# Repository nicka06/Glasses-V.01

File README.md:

# Glasses-V.01

This repo shows a pair of "AI" glasses that use a microphone, speaker, and microcontroller to allow users to have siri at all times (when on wifi). They'll be able to ask questions, complete tasks, and be more efficient with these glasses. While these glasses have only audio, it is a first step towareds glasses with cameras and more. This is my personal end goal for this project. Just a stepping stone towards more advance glasses work. (Hence the V0.1 repo name). If you have any questions, feel free to reach out. 

|Part                        |Part Number                             |# of parts|snapeda link                                                                                                                                                                                                                                                                                                                                                                                                                                                                                                                                                                                                                                                                           |Price|Actual Link                                                                                                                                                                                                                                                                                                                                                                                                                                                                                                                                                                                                                                                                            |Total Price|
|----------------------------|----------------------------------------|----------|---------------------------------------------------------------------------------------------------------------------------------------------------------------------------------------------------------------------------------------------------------------------------------------------------------------------------------------------------------------------------------------------------------------------------------------------------------------------------------------------------------------------------------------------------------------------------------------------------------------------------------------------------------------------------------------|-----|---------------------------------------------------------------------------------------------------------------------------------------------------------------------------------------------------------------------------------------------------------------------------------------------------------------------------------------------------------------------------------------------------------------------------------------------------------------------------------------------------------------------------------------------------------------------------------------------------------------------------------------------------------------------------------------|-----------|
|Microcontroller             |ESP32-S3-WROOM-1-N16R8                  |1         |https://www.snapeda.com/parts/ESP32-S3-WROOM-1-N16R8/Espressif%20Systems/view-part/?ref=search&t=ESP32-S3-WROOM-1-N16R8&ab_test_case=b                                                                                                                                                                                                                                                                                                                                                                                                                                                                                                                                                 |6.56 |https://www.digikey.com/en/products/detail/espressif-systems/ESP32-S3-WROOM-1-N16R8/16163954?gad_source=1&gad_campaignid=20783325532&gbraid=0AAAAADrbLlhoX6jquTGZxW9rgvqGXhdUZ&gclid=CjwKCAjwp_LDBhBCEiwAK7Fnkuxh-Wv312ccLeRvQl4KA0CQU8T0WVN-HfHrd-JbklPjBEjkM-3N1hoC2ZgQAvD_BwE&gclsrc=aw.ds                                                                                                                                                                                                                                                                                                                                                                                          |13.12      |
|Microphone                  |ICS-43434                               |1         |https://www.snapeda.com/parts/ICS-43434/TDK%20InvenSense/view-part/?ref=tdk%20invensense_in&t=ICS-43434&con_ref=None                                                                                                                                                                                                                                                                                                                                                                                                                                                                                                                                                                   |2.98 |https://www.digikey.com/en/products/detail/tdk-invensense/ICS-43434/6140298?utm_campaign=buynow&utm_medium=aggregator&utm_source=snapeda                                                                                                                                                                                                                                                                                                                                                                                                                                                                                                                                               |5.96       |
|Amplifier                   |MAX98357AETE+T                          |1         |http://snapeda.com/parts/MAX98357AETE%2BT/Analog%20Devices/view-part/?ref=search&t=MAX98357AETE%2BT&ab_test_case=b                                                                                                                                                                                                                                                                                                                                                                                                                                                                                                                                                                     |3.19 |https://www.digikey.com/en/products/detail/analog-devices-inc-maxim-integrated/MAX98357AETE-T/4936122?utm_campaign=buynow&utm_medium=aggregator&utm_source=snapeda                                                                                                                                                                                                                                                                                                                                                                                                                                                                                                                     |6.38       |
|Speaker                     |KDMG151508-05                           |1         |https://www.snapeda.com/parts/KDMG151508-05/Kingstate/view-part/?ref=search&t=KDMG151508-05                                                                                                                                                                                                                                                                                                                                                                                                                                                                                                                                                                                            |2.12 |https://www.digikey.com/en/products/detail/db-unlimited/SM150908-2/9990586?gad_source=1&gad_campaignid=20243136172&gbraid=0AAAAADrbLlgid6KqDNBHULPHGtDjBGKy6&gclid=CjwKCAjwp_LDBhBCEiwAK7Fnknqfs3PqYxI0d2qcRMip4_ntUb9yY7HQQ-hDFoptXZGg9NlflI530RoCsUwQAvD_BwE&gclsrc=aw.ds                                                                                                                                                                                                                                                                                                                                                                                                            |4.24       |
|Battery                     |1570 Lithium Polymer Battery 3.7V 100mAh|1         |https://www.snapeda.com/parts/1570/Adafruit%20Industries/view-part/?ref=search&t=Lithium%20Ion%20Polymer%20Battery%20with%20Short%20Cable%20-%203.7V%20200mAh&ab_test_case=b                                                                                                                                                                                                                                                                                                                                                                                                                                                                                                           |5.95 |https://www.digikey.com/en/products/detail/adafruit-industries-llc/1570/5054546?utm_campaign=buynow&utm_medium=aggregator&utm_source=snapeda                                                                                                                                                                                                                                                                                                                                                                                                                                                                                                                                           |11.9       |
|Charge Management Controller|MCP73831T-2ACI/OT                       |1         |https://www.snapeda.com/parts/MCP73831T-2ACI/OT/Microchip%20Technology/view-part/?ref=search&t=MCP73831&ab_test_case=b                                                                                                                                                                                                                                                                                                                                                                                                                                                                                                                                                                 |0.76 |https://www.digikey.com/en/products/detail/microchip-technology/MCP73831T-2ACI-OT/964301?utm_campaign=buynow&utm_medium=aggregator&utm_source=snapeda                                                                                                                                                                                                                                                                                                                                                                                                                                                                                                                                  |1.52       |
|                            |TLV62568DBVR                            |1         |https://www.snapeda.com/parts/2340901-1/TE%20Connectivity/view-part/?ref=search&t=2340901-1&ab_test_case=b                                                                                                                                                                                                                                                                                                                                                                                                                                                                                                                                                                             |0.23 |https://www.digikey.com/en/products/detail/texas-instruments/TLV62568DBVR/6588886?utm_campaign=buynow&utm_medium=aggregator&utm_source=snapeda                                                                                                                                                                                                                                                                                                                                                                                                                                                                                                                                         |0.46       |
|USB C Port                  |2340901-1                               |1         |https://www.snapeda.com/parts/2340901-1/TE%20Connectivity/view-part/?ref=search&t=2340901-1&ab_test_case=b                                                                                                                                                                                                                                                                                                                                                                                                                                                                                                                                                                             |0.7  |https://www.digikey.com/en/products/detail/gct/USB4500-03-0-A/15283206                                                                                                                                                                                                                                                                                                                                                                                                                                                                                                                                                                                                                 |1.4        |
|Battery Connector (white)   |B2B-PH-K-S (LF)(SN)                     |1         |https://www.snapeda.com/parts/B2B-PH-K-S%20%28LF%29%28SN%29/JST/view-part/?ref=search&t=B2B-PH-K-S&ab_test_case=b                                                                                                                                                                                                                                                                                                                                                                                                                                                                                                                                                                      |0.1  |https://www.digikey.com/en/products/detail/jst-sales-america-inc/B2B-XH-A/1651045?gad_source=1&gad_campaignid=20783325532&gbraid=0AAAAADrbLlhoX6jquTGZxW9rgvqGXhdUZ&gclid=CjwKCAjwp_LDBhBCEiwAK7FnkiGOrYvskTYfoYS7-Bnt9eSlk76hj8uJJX4-BQsrg9oAHQYzmg24FBoCVZsQAvD_BwE&gclsrc=aw.ds                                                                                                                                                                                                                                                                                                                                                                                                     |0.2        |
|Manual Switch               |PCM12SMTR                               |1         |https://www.snapeda.com/parts/PCM12SMTR/Littelfuse%2FC%26K/view-part/?ref=search&t=PCM12SMTR&ab_test_case=b                                                                                                                                                                                                                                                                                                                                                                                                                                                                                                                                                                            |0.8  |https://www.snapeda.com/parts/PCM12SMTR/Littelfuse%2FC%26K/view-part/?ref=search&t=PCM12SMTR&ab_test_case=b                                                                                                                                                                                                                                                                                                                                                                                                                                                                                                                                                                            |1.6        |
|LED Blue Light              |LTST-C191TBKT                           |1         |https://www.snapeda.com/parts/LTST-C191TBKT/Lite-On%20Electronics/view-part/?ref=dk&t=LTST-C191TBKT&con_ref=None&ab_test_case=b                                                                                                                                                                                                                                                                                                                                                                                                                                                                                                                                                        |0.24 |https://www.digikey.com/en/products/detail/liteon/LTST-C191TBKT/388530?utm_source=snapeda&utm_medium=aggregator&utm_campaign=buynow                                                                                                                                                                                                                                                                                                                                                                                                                                                                                                                                                    |0.48       |
|LED Red Light               |LTST-C191KRKT                           |1         |https://www.snapeda.com/parts/LTST-C191KRKT/Lite-On%20Inc./view-part/?ref=dk&t=LTST-C191KRKT&con_ref=None&ab_test_case=b                                                                                                                                                                                                                                                                                                                                                                                                                                                                                                                                                               |0.15 |https://www.digikey.com/en/products/detail/liteon/LTST-C191KRKT/386837?utm_source=snapeda&utm_medium=aggregator&utm_campaign=buynow                                                                                                                                                                                                                                                                                                                                                                                                                                                                                                                                                    |0.3        |
|5.1k Resistor               |ERA-3ARB512V                            |3         |https://www.snapeda.com/parts/ERA-3ARB512V/Panasonic/view-part/?ref=search&t=ERA-3ARB512V&ab_test_case=b                                                                                                                                                                                                                                                                                                                                                                                                                                                                                                                                                                               |0.35 |https://www.digikey.com/en/products/detail/panasonic-electronic-components/ERA-3ARB512V/3073669?utm_campaign=buynow&utm_medium=aggregator&utm_source=snapeda                                                                                                                                                                                                                                                                                                                                                                                                                                                                                                                           |2.1        |
|10k resistor                |CR0603AFX-1002EAS                       |2         |https://www.snapeda.com/parts/CR0603AFX-1002EAS/Bourns/view-part/?ref=search&t=CR0603AFX-1002EAS&ab_test_case=b                                                                                                                                                                                                                                                                                                                                                                                                                                                                                                                                                                        |0.1  |https://www.digikey.com/en/products/detail/bourns-inc/CR0603AFX-1002EAS/10240117?utm_campaign=buynow&utm_medium=aggregator&utm_source=snapeda                                                                                                                                                                                                                                                                                                                                                                                                                                                                                                                                          |0.4        |
|220hms Resistor             |WK73R1JTTD2200F                         |2         |https://www.snapeda.com/parts/WK73R1JTTD2200F/KOA%20Speer/view-part/?ref=search&t=WK73R1JTTD2200F&ab_test_case=b                                                                                                                                                                                                                                                                                                                                                                                                                                                                                                                                                                       |0.12 |https://www.mouser.com/ProductDetail/KOA-Speer/WK73R1JTTD2200F?utm_campaign=mouser&qs=xhbEVWpZdWcwQMv%2FxntCbQ%3D%3D&utm_medium=online&utm_source=snapedaonline&utm_content=model                                                                                                                                                                                                                                                                                                                                                                                                                                                                                                      |0.48       |
|100nf capacitor             |885012206071                            |4         |https://www.snapeda.com/parts/885012206071/W%C3%BCrth%20Elektronik/view-part/?ref=dk&t=%200603%20Ceramic%20100nF&con_ref=None&ab_test_case=b                                                                                                                                                                                                                                                                                                                                                                                                                                                                                                                                           |0.1  |https://www.digikey.com/en/products/detail/w%C3%BCrth-elektronik/885012206071/5453844?utm_source=snapeda&utm_medium=aggregator&utm_campaign=buynow                                                                                                                                                                                                                                                                                                                                                                                                                                                                                                                                     |0.8        |
|4.7u capitor                |CL10A475KA8NQNC                         |1         |https://www.snapeda.com/parts/CL10A475KA8NQNC/Samsung/view-part/?ref=me&t=%200603%20Ceramic%204.7%C2%B5F&con_ref=None&ab_test_case=b                                                                                                                                                                                                                                                                                                                                                                                                                                                                                                                                                   |0.23 |https://www.mouser.com/ProductDetail/Samsung-Electro-Mechanics/CL10A475KA8NQNC?qs=9nYkJLYMUzsiOkP%2FacWBkg%3D%3D&utm_source=snapedaonline&utm_medium=online&utm_campaign=mouser&utm_content=partpage                                                                                                                                                                                                                                                                                                                                                                                                                                                                                   |0.46       |
|10uf capictor               |GRM188R61A106MAALD                      |2         |https://www.snapeda.com/parts/GRM188R61A106MAALD/Murata/view-part/?ref=dk&t=%200603%20Ceramic%2010%C2%B5F&con_ref=None&ab_test_case=b                                                                                                                                                                                                                                                                                                                                                                                                                                                                                                                                                  |0.22 |https://www.digikey.com/en/products/detail/murata-electronics/GRM188R61A106MAALD/4905335?utm_source=snapeda&utm_medium=aggregator&utm_campaign=buynow                                                                                                                                                                                                                                                                                                                                                                                                                                                                                                                                  |0.88       |
|22uf capictor               |C1608X5R0J226M080AC                     |1         |https://www.snapeda.com/parts/C1608X5R0J226M080AC/TDK/view-part/?ref=dk&t=%200603%20Ceramic%2022%C2%B5F&con_ref=None&ab_test_case=b                                                                                                                                                                                                                                                                                                                                                                                                                                                                                                                                                    |0.27 |https://www.digikey.com/en/products/detail/tdk-corporation/C1608X5R0J226M080AC/2792254?utm_source=snapeda&utm_medium=aggregator&utm_campaign=buynow                                                                                                                                                                                                                                                                                                                                                                                                                                                                                                                                    |0.54       |
|2.2 inductor                |DFE252012F-2R2M=P2                      |1         |https://www.snapeda.com/parts/DFE252012F-2R2M%3DP2/Murata/view-part/?ref=search&t=DFE252012F-2R2M%3DP2&ab_test_case=b                                                                                                                                                                                                                                                                                                                                                                                                                                                                                                                                                                  |0.24 |https://www.digikey.com/en/products/detail/murata-electronics/DFE252012F-2R2M-P2/5812591?utm_campaign=buynow&utm_medium=aggregator&utm_source=snapeda                                                                                                                                                                                                                                                                                                                                                                                                                                                                                                                                  |0.48       |
|ESD Protector               |TPD2E001DRLRG4                          |1         |https://www.snapeda.com/parts/TPD2E001DRLRG4/Texas%20Instruments/view-part/?ref=search&t=TPD2E001DRLR&ab_test_case=b                                                                                                                                                                                                                                                                                                                                                                                                                                                                                                                                                                   |0.77 |https://www.digikey.com/en/products/detail/texas-instruments/TPD2E001DRLRG4/1907452?utm_campaign=buynow&utm_medium=aggregator&utm_source=snapeda                                                                                                                                                                                                                                                                                                                                                                                                                                                                                                                                       |1.54       |
|1u capitor                  |885012206026                            |1         |https://www.snapeda.com/parts/885012206026/W%C3%BCrth%20Elektronik/view-part/?ref=search&t=1%C2%B5F%2010V%200603%20ceramic%20capacitor&ab_test_case=b                                                                                                                                                                                                                                                                                                                                                                                                                                                                                                                                  |0.27 |https://www.digikey.com/en/products/detail/w%C3%BCrth-elektronik/885012206026/5453800?utm_campaign=buynow&utm_medium=aggregator&utm_source=snapeda                                                                                                                                                                                                                                                                                                                                                                                                                                                                                                                                     |0.54       |
|Switch Button               |TL3315NF160Q                            |1         |https://www.snapeda.com/parts/TL3315NF160Q/E-Switch/view-part/?ref=search&t=tl3315nf160Q                                                                                                                                                                                                                                                                                                                                                                                                                                                                                                                                                                                               |0.15 |https://www.digikey.com/en/products/detail/e-switch/TL3315NF160Q/1870395?utm_campaign=buynow&utm_medium=aggregator&utm_source=snapeda                                                                                                                                                                                                                                                                                                                                                                                                                                                                                                                                                  |0.3        |
|3d Printing filament        |N/A                                     |1         |https://www.amazon.com/eSUN-Filament-Printing-Printer-Designed/dp/B0DGQBMJMK/ref=sr_1_16?dib=eyJ2IjoiMSJ9.Razt1k5uVOV2TzDUjSQvl7XEcxdtlHmAdZQWosMeTQ50CwFn7o1y91poBYqmVyD9HxIA_A0r02FOmVlrp1nPMesRN62hAAydwv-PxE5Qi07-Ww0ryQYsGgAqZsrmEU20zU0_ffjW8d8uhPSc8SdO0CSTQG0t-tMYp2xMcieXr8z_RaTrzCr2jQG8r_7wSBk8uNSQbhB2PLppIrgodCKK9YNonEEP75L9N3QZLqYCnD0.fJtDJZ7egESpQDcGEz5eu_KVAuM1CXnrID5a33sKsjs&dib_tag=se&hvadid=695206731837&hvdev=c&hvexpln=67&hvlocphy=9190255&hvnetw=g&hvocijid=9219964727381373825--&hvqmt=e&hvrand=9219964727381373825&hvtargid=kwd-320787596539&hydadcr=8497_13654088&keywords=pla%2Bamazon&mcid=987f97c45f7b3a3dac93ebf26610d89d&qid=1754454039&sr=8-16&th=1|11.39|https://www.amazon.com/eSUN-Filament-Printing-Printer-Designed/dp/B0DGQBMJMK/ref=sr_1_16?dib=eyJ2IjoiMSJ9.Razt1k5uVOV2TzDUjSQvl7XEcxdtlHmAdZQWosMeTQ50CwFn7o1y91poBYqmVyD9HxIA_A0r02FOmVlrp1nPMesRN62hAAydwv-PxE5Qi07-Ww0ryQYsGgAqZsrmEU20zU0_ffjW8d8uhPSc8SdO0CSTQG0t-tMYp2xMcieXr8z_RaTrzCr2jQG8r_7wSBk8uNSQbhB2PLppIrgodCKK9YNonEEP75L9N3QZLqYCnD0.fJtDJZ7egESpQDcGEz5eu_KVAuM1CXnrID5a33sKsjs&dib_tag=se&hvadid=695206731837&hvdev=c&hvexpln=67&hvlocphy=9190255&hvnetw=g&hvocijid=9219964727381373825--&hvqmt=e&hvrand=9219964727381373825&hvtargid=kwd-320787596539&hydadcr=8497_13654088&keywords=pla%2Bamazon&mcid=987f97c45f7b3a3dac93ebf26610d89d&qid=1754454039&sr=8-16&th=1|11.39      |
|PCB                         |N/A                                     |1         |N/A                                                                                                                                                                                                                                                                                                                                                                                                                                                                                                                                                                                                                                                                                    |2    |N/A                                                                                                                                                                                                                                                                                                                                                                                                                                                                                                                                                                                                                                                                                    |2          |
|                            |                                        |          |                                                                                                                                                                                                                                                                                                                                                                                                                                                                                                                                                                                                                                                                                       |     |                                                                                                                                                                                                                                                                                                                                                                                                                                                                                                                                                                                                                                                                                       |69.47      |
                                                                                                                                                                                                                                                                                    |56.08      |

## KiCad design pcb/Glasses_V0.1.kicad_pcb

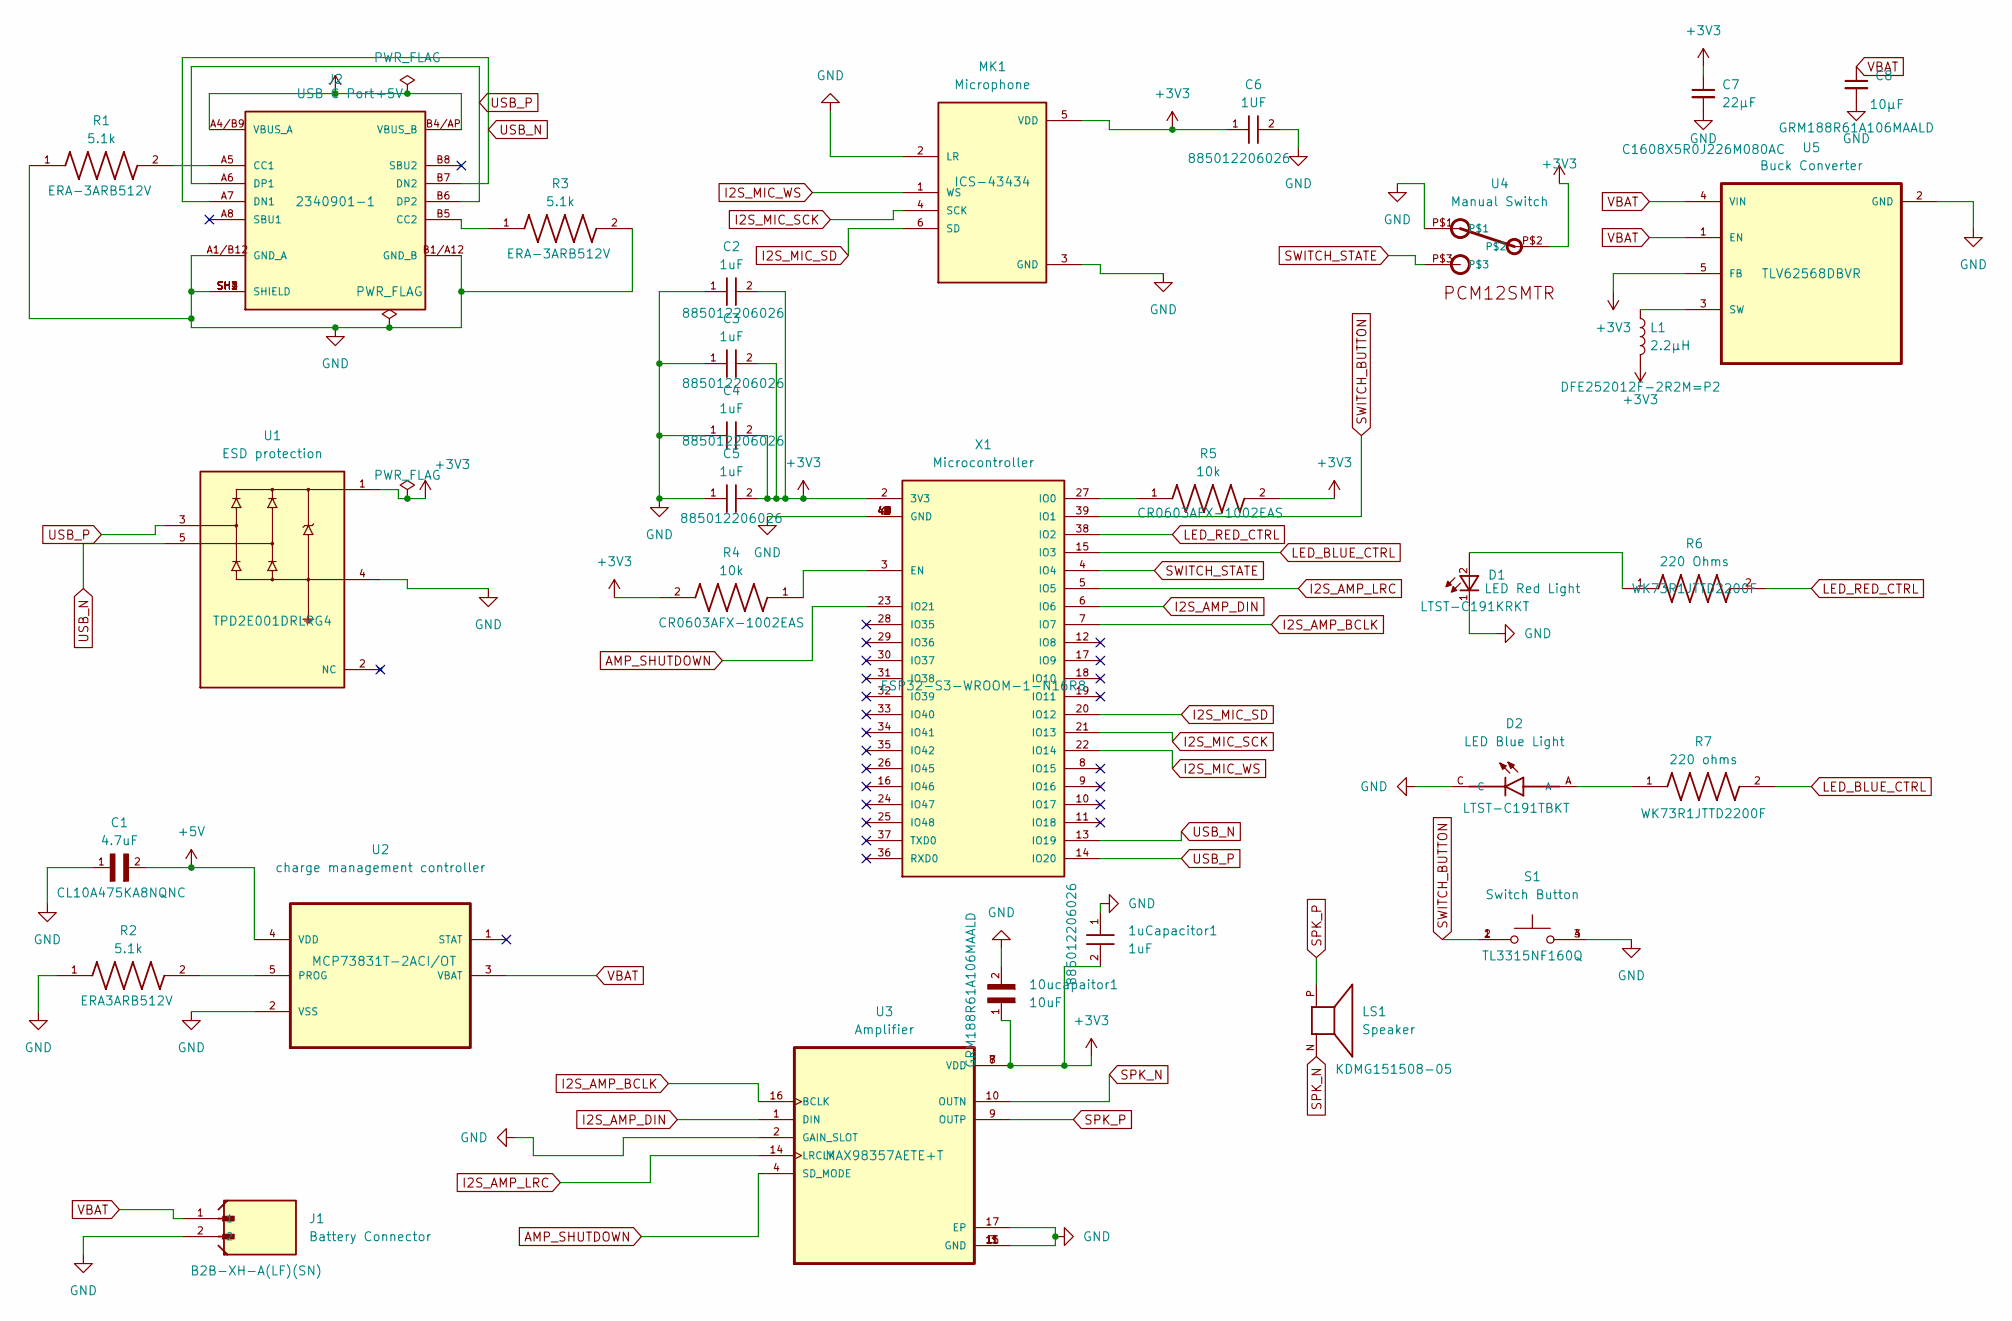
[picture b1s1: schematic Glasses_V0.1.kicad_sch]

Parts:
1uCapacitor1: 1uF; WCAP-CSGP_0603_R
10ucapaitor1: 10uF; CAPC1608X95N; DigiKey_Part_Number 490-12734-2-ND
C1: 4.7uF; CAPC1608X100N
C2, C3, C4, C5: 1uF; WCAP-CSGP_0603_R
C6: 1UF; WCAP-CSGP_0603_R
C7: 22µF; CAPC1608X100N
C8: 10µF; CAPC1608X95N
D1: LED Red Light; 0603; DigiKey_Part_Number 160-1447-2-ND
D2: LED Blue Light; LEDC1608X65N; DigiKey_Part_Number 160-1647-2-ND
J1: Battery Connector; JST_B2B-PH-K-S_LF__SN_
J2: USB C Port; TE_2340901-1; PARTREV A
L1: 2.2µH; INDC2520X120N
LS1: Speaker; SPKR_KDMG151508-05; PARTREV 1.1
MK1: Microphone; MIC_ICS-43434
R1, R2, R3: 5.1k; RES_ERA3ARB512V; PARTREV 3/1/2020
R4, R5: 10k; RESC1608X55N
R6: 220 Ohms; RESC0816X55N
R7: 220 ohms; RESC0816X55N
S1: Switch Button; SW_TL3315NF160Q; PARTREV B
U1: ESD protection; SOTFL50P160X60-5N; PARTREV I
U2: charge management controller; SOT95P280X145-5N; MPN MCP73831T-2ACI/OT
U3: Amplifier; QFN50P300X300X80-17N
U4: Manual Switch; PCM12SMTR
U5: Buck Converter; SOT95P280X145-5N
X1: Microcontroller; ESP32S3WROOM1N8R2; MANUFACTURER_PART_NUMBER ESP32-S3-WROOM-1-N16R8

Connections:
+3V3: 1uCapacitor1.2, 10ucapaitor1.1, C2.2, C3.2, C4.2, C5.2, C6.1, C7.1, L1.2, MK1.5 (VDD), R4.2, R5.2, U1.1, U3.7 (VDD), U3.8 (VDD), U4.P$2, U5.5 (FB), X1.2 (3V3)
+5V: C1.2, J2.A4/B9 (VBUS_A), J2.B4/AP (VBUS_B), U2.4 (VDD)
AMP_SHUTDOWN: U3.4 (SD_MODE), X1.23 (IO21)
GND: 1uCapacitor1.1, 10ucapaitor1.2, C1.1, C2.1, C3.1, C4.1, C5.1, C6.2, C7.2, C8.2, D1.1, D2.C, J1.2, J2.A1/B12 (GND_A), J2.B1/A12 (GND_B), J2.SH1 (SHIELD), J2.SH2 (SHIELD), J2.SH3 (SHIELD), J2.SH4 (SHIELD), MK1.2 (LR), MK1.3 (GND), R1.1, R2.1, R3.2, S1.3, S1.4, U1.4, U2.2 (VSS), U3.2 (GAIN_SLOT), U3.3 (GND), U3.11 (GND), U3.15 (GND), U3.17 (EP), U4.P$1, U5.2 (GND), X1.1 (GND), X1.40 (GND), X1.41 (GND), X1.42 (GND), X1.43 (GND), X1.44 (GND), X1.45 (GND), X1.46 (GND), X1.47 (GND), X1.48 (GND), X1.49 (GND)
I2S_AMP_BCLK: U3.16 (BCLK), X1.7 (IO7)
I2S_AMP_DIN: U3.1 (DIN), X1.6 (IO6)
I2S_AMP_LRC: U3.14 (LRCLK), X1.5 (IO5)
I2S_MIC_SCK: MK1.4 (SCK), X1.21 (IO13)
I2S_MIC_SD: MK1.6 (SD), X1.20 (IO12)
I2S_MIC_WS: MK1.1 (WS), X1.22 (IO14)
LED_BLUE_CTRL: R7.2, X1.15 (IO3)
LED_RED_CTRL: R6.2, X1.38 (IO2)
unnamed: D1.2, R6.1
unnamed: D2.A, R7.1
unnamed: J2.A5 (CC1), R1.2
unnamed: J2.B5 (CC2), R3.1
unnamed: R2.2, U2.5 (PROG)
unnamed: L1.1, U5.3 (SW)
unnamed: R4.1, X1.3 (EN)
unnamed: R5.1, X1.27 (IO0)
SPK_N: LS1.N, U3.10 (OUTN)
SPK_P: LS1.P, U3.9 (OUTP)
SWITCH_BUTTON: S1.1, S1.2, X1.39 (IO1)
SWITCH_STATE: U4.P$3, X1.4 (IO4)
USB_N: J2.A7 (DN1), J2.B7 (DN2), U1.5, X1.13 (IO19)
USB_P: J2.A6 (DP1), J2.B6 (DP2), U1.3, X1.14 (IO20)
VBAT: C8.1, J1.1, U2.3 (VBAT), U5.1 (EN), U5.4 (VIN)

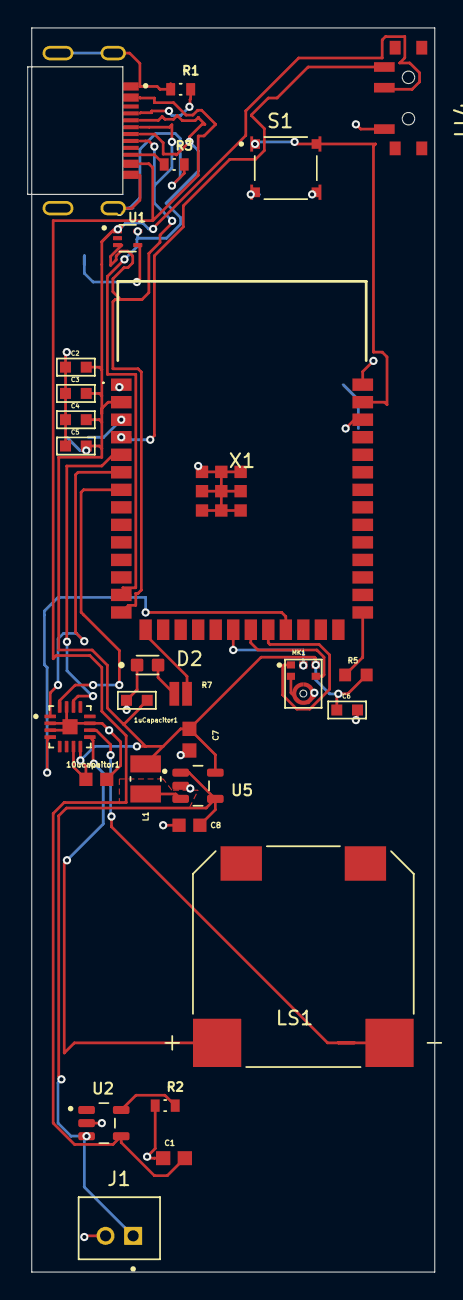
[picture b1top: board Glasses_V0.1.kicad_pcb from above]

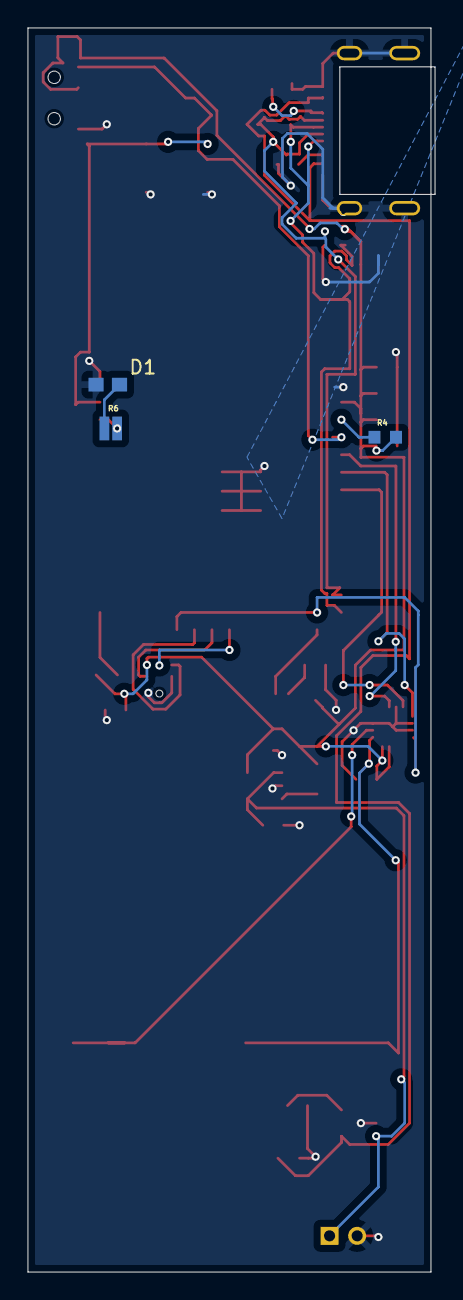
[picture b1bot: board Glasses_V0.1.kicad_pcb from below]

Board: 2 copper layers, 29.2 x 90.2 mm, 31 parts (3 on the bottom side), 27 nets.

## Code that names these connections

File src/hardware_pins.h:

#pragma once // Prevents the file from being included multiple times

// --- LED Pins ---
const int LED_RED_PIN = 38;
const int LED_BLUE_PIN = 15;

// --- Switch & Button Pins ---
const int SWITCH_STATE_PIN = 4;   // Manual slide switch
const int SWITCH_BUTTON_PIN = 39;  // Momentary push button

// --- Amplifier (Speaker) Pins ---
const int AMP_SHUTDOWN_PIN = 23;
// I2S is a protocol for audio
const int I2S_AMP_BCLK_PIN = 7;  // Bit Clock
const int I2S_AMP_LRC_PIN = 5;   // Left/Right Clock (Word Select)
const int I2S_AMP_DIN_PIN = 6;   // Data In

// --- Microphone Pins ---
const int I2S_MIC_SD_PIN = 20;   // Serial Data
const int I2S_MIC_SCK_PIN = 21;  // Serial Clock
const int I2S_MIC_WS_PIN = 22;   // Word Select

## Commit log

2025-07-20 first version of firmware
2025-07-20 updated gitignore
2025-07-20 Apply .gitignore and re-track files
2025-07-20 Updated Title Info
2025-07-20 Create bill_of_materials
2025-07-20 Update .gitignore to track project folders
2025-07-20 Fix .gitignore to correctly track project folders
2025-07-20 Refine .gitignore to only track essential project folders
2025-07-20 Fix .gitignore and track all project files
2025-07-20 Stop tracking build and config files
2025-07-20 adding bill of materials :
2025-07-23 Update bill_of_materials to be accurate
2025-07-27 Update and rename AR Glasses BOM - Sheet1 (2).csv to AR Glasses BOM
2025-07-27 updated step files
2025-07-27 updated the bom's name
2025-08-15 Updated to connect to chatgpt directly via wifi
